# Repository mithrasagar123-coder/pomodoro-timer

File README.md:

# Pomodoro Timer

## Overview
Classic study timer using the Pomodoro technique, built with an OLED screen and 4 buttons to cycle between focus and breaks.

I designed this for my Week 4 project of halflife, a 10-week program where you can design and build hardware projects free of cost!

## Parts
* Seeed Studio XIAO-ESP32-C3 as the main microcontroller
* 0.96 inch OLED Display with the timer
* Four buttons: first enters focus mode, second enters short break, third enters long break, and the last resets the timer.
* Keycaps built with CAD

## Schematic 

## Board

*(The character shown twice is Kanade Yoisaki from Project Sekai. The first image depicts her with her phone, representing break time, and the second image shows her intensely reading a book, representing focus time.)* 

## Code

| Control | What it does |
| --- | --- |
| Button 1 | Starts focus mode for 25 minutes. Once timer goes to 0, short break automatically starts. |
| Button 2 | Pauses focus timer and starts short break for 5 minutes. Focus mode will continue when short break is over. |
| Button 3 | Pauses focus timer and starts long break for 15 minutes.  |
| Button 4 | Resets all timers. |

View the entire thing at [sketch_pomodorotimer.ino](https://github.com/mithrasagar123-coder/pomodoro-timer/blob/main/sketch_pomodorotimer.ino).

## Keycaps

To be printed and placed on the buttons:

## BOM
| Item | Qty | Supplier | Cost/item | Total Cost | Link |
|:---|:---|:---|:---|:---|:---|
| Seeed Studio XIAO-ESP32-C3 | 1 | Seeed Studio | $4.99 | $4.99 | https://www.seeedstudio.com/Seeed-XIAO-ESP32C3-p-5431.html |
| 0.96-inch OLED Display | 1 | AliExpress | $2.79 | $2.79 | https://www.aliexpress.us/item/3256805954920554.html?spm=a2g0o.productlist.main.1.32b8a8e5Y5o9Hk&algo_pvid=7068df0e-a7e9-40a5-a501-8025acc785f3&algo_exp_id=7068df0e-a7e9-40a5-a501-8025acc785f3-0&pdp_ext_f=%7B%22order%22%3A%2225896%22%2C%22eval%22%3A%221%22%2C%22fromPage%22%3A%22search%22%7D&pdp_npi=6%40dis%21USD%212.79%211.09%21%21%2118.49%217.24%21%402101c28d17935965783886997e0d81%2112000035944225407%21sea%21US%218341090660%21ABX%211%210%21n_tag%3A-29910%3Bd%3A87101d9a%3Bm03_new_user%3A-29895%3BpisId%3A5000000218165391&curPageLogUid=tt2hJtQ4NrUw&utparam-url=scene%3Asearch%7Cquery_from%3A%7Cx_object_id%3A1005006141235306%7C_p_origin_prod%3A |
| Kailh Choc Low-Profile Switches | 1 | AliExpress | $3.99 | $3.99 | https://www.aliexpress.us/item/3256812653947991.html?spm=a2g0o.productlist.main.5.46583c5f4cJJz8&algo_pvid=ebc10692-7dcd-47ba-b681-e56178b7efc4&algo_exp_id=ebc10692-7dcd-47ba-b681-e56178b7efc4-4&pdp_ext_f=%7B%22order%22%3A%2254%22%2C%22eval%22%3A%221%22%2C%22fromPage%22%3A%22search%22%7D&pdp_npi=6%40dis%21USD%214.36%211.09%21%21%214.36%211.09%21%402103119c17929747023374751e0eba%2112000059499320560%21sea%21US%218341090660%21ABX%211%210%21n_tag%3A-29910%3Bd%3A87101d9a%3Bm03_new_user%3A-29895%3BpisId%3A5000000218165390&curPageLogUid=EVQYU9kkAF7W&utparam-url=scene%3Asearch%7Cquery_from%3A%7Cx_object_id%3A1005012840262743%7C_p_origin_prod%3A |
| CAD Keycaps | 1 | Local 3D Printing | $5.00 | $5.00 | https://shop.local3dprinting.com/checkouts/do/81122164dba6abff0cd510225204afb7/en-us?auto_redirect=false&edge_redirect=true&skip_shop_pay=true |
| PCB | 1 | JLCPCB | $4.00 | $4.00 | https://cart.jlcpcb.com/quote?stencilLayer=2&stencilWidth=100&stencilLength=100&stencilCounts=5&plateType=1&spm=Jlcpcb.Homepage.1010 |
| Estimated total shipping |  |  |  | $9.71 |  |
| **Total** |  |  |  | **$30.48** |  |

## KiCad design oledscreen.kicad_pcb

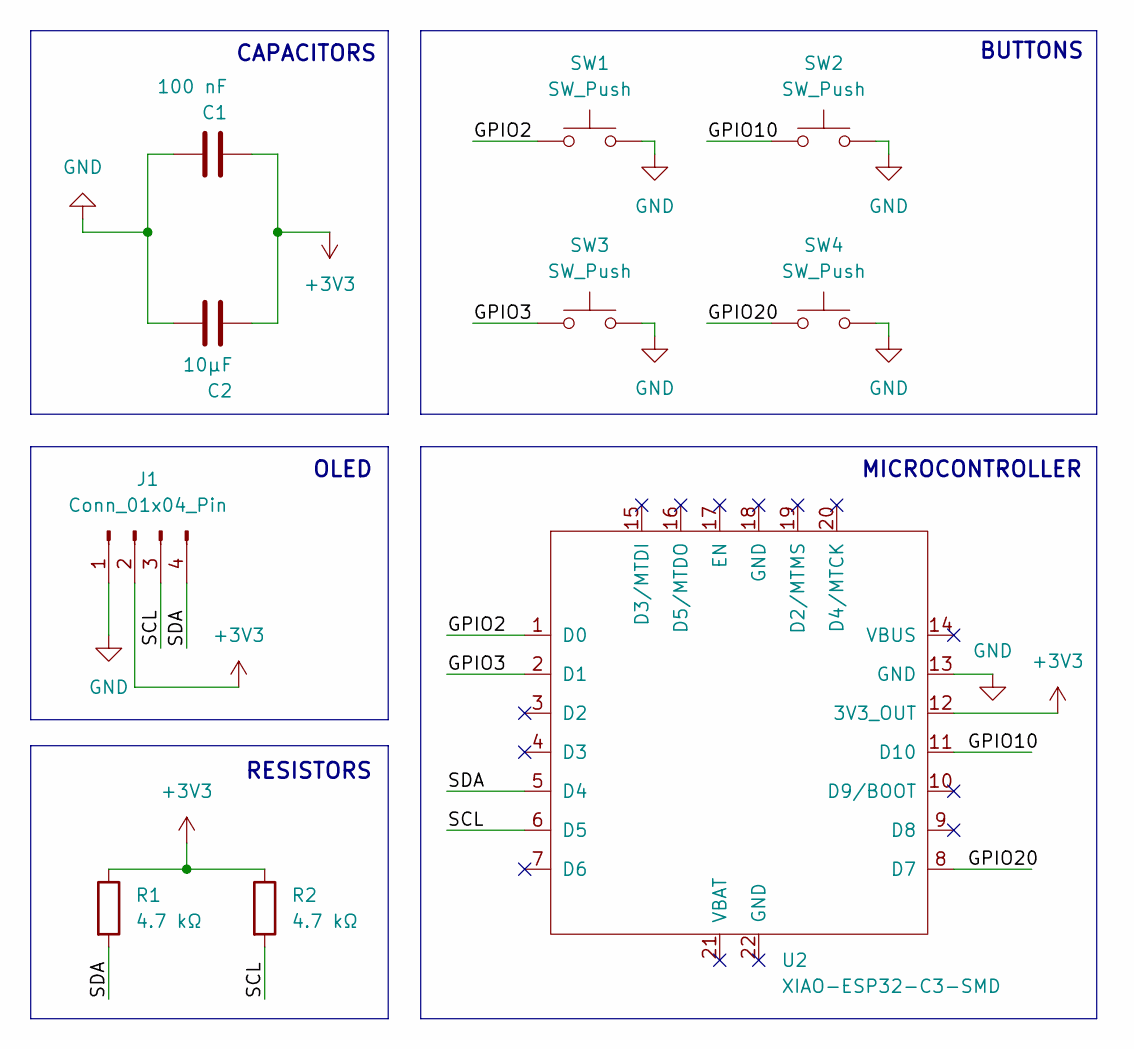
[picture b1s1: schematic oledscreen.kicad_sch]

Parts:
C1: 100 nF; C_0805_2012Metric
C2: 10µF; C_0805_2012Metric
J1: Conn_01x04_Pin; Display_128x64_096_I2C
R1, R2: 4.7 kΩ; R_0805_2012Metric
SW1, SW2, SW3, SW4: SW_Push; Kailh Choc Low-Profile Switches
U2: XIAO-ESP32-C3-SMD; XIAO-ESP32-C6-DIP

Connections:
+3V3: C1.1, C2.1, J1.2, R1.1, R2.1, U2.12 (3V3_OUT)
/GPIO2: SW1.1, U2.1 (D0)
/GPIO3: SW3.1, U2.2 (D1)
/GPIO10: SW2.1, U2.11 (D10)
/GPIO20: SW4.1, U2.8 (D7)
/SCL: J1.3, R2.2, U2.6 (D5)
/SDA: J1.4, R1.2, U2.5 (D4)
GND: C1.2, C2.2, J1.1, SW1.2, SW2.2, SW3.2, SW4.2, U2.13 (GND)

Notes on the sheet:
MICROCONTROLLER
RESISTORS
BUTTONS
OLED
CAPACITORS

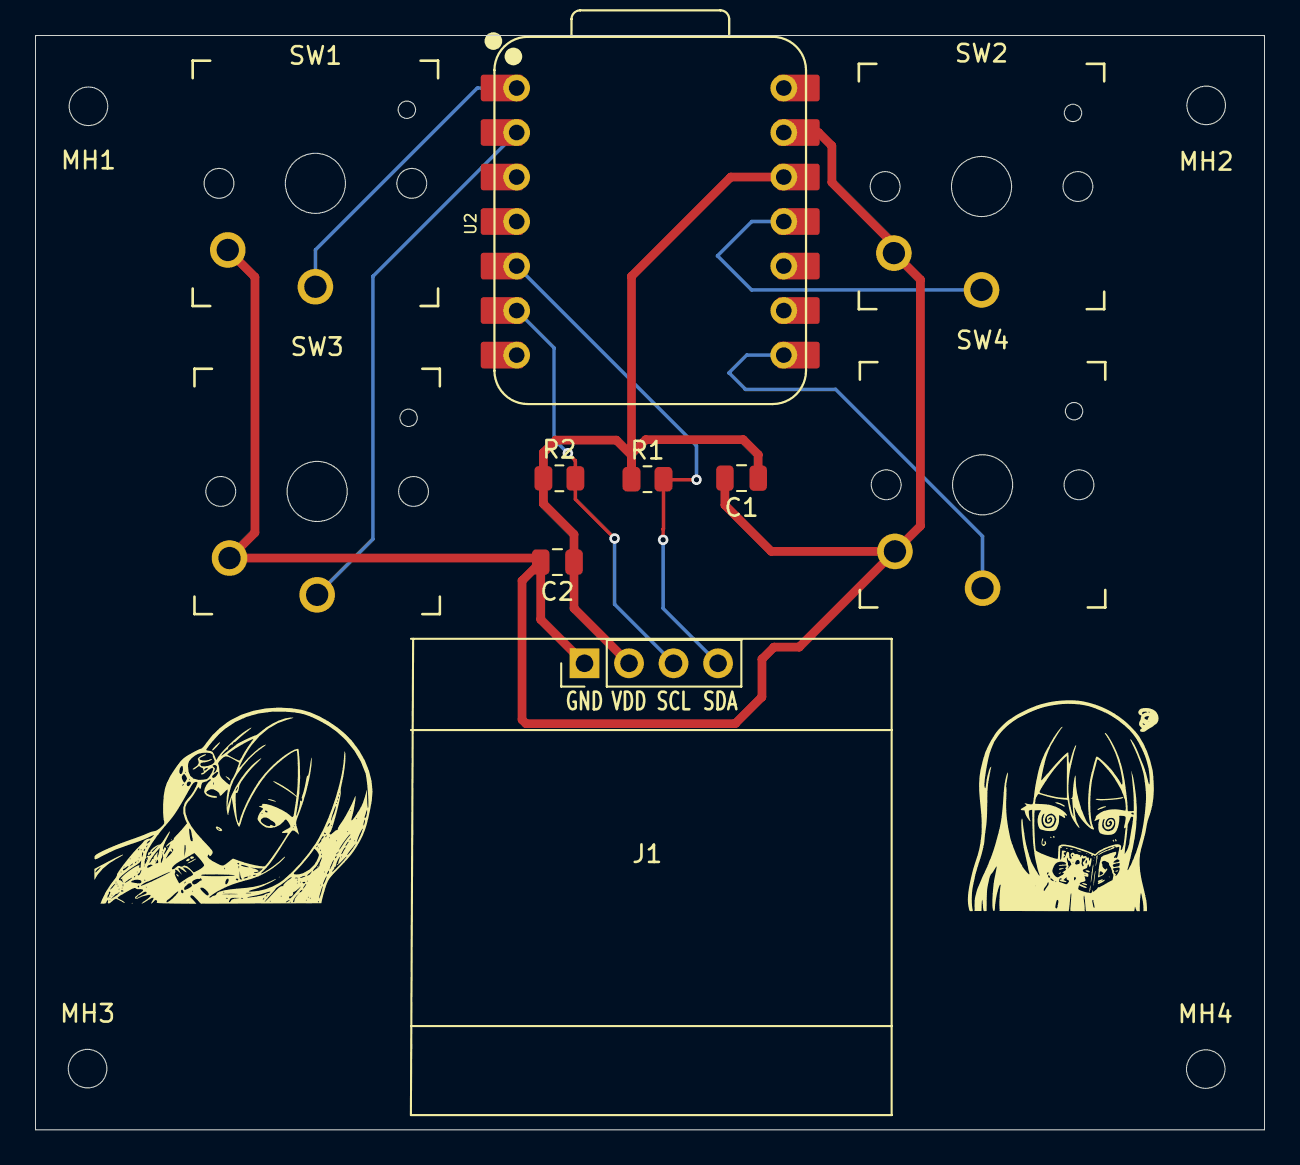
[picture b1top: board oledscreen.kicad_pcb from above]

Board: 2 copper layers, 70.1 x 62.4 mm, 14 parts (0 on the bottom side), 8 nets.

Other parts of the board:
MH1, MH2, MH3, MH4: MountingHole_2.2mm_M2
